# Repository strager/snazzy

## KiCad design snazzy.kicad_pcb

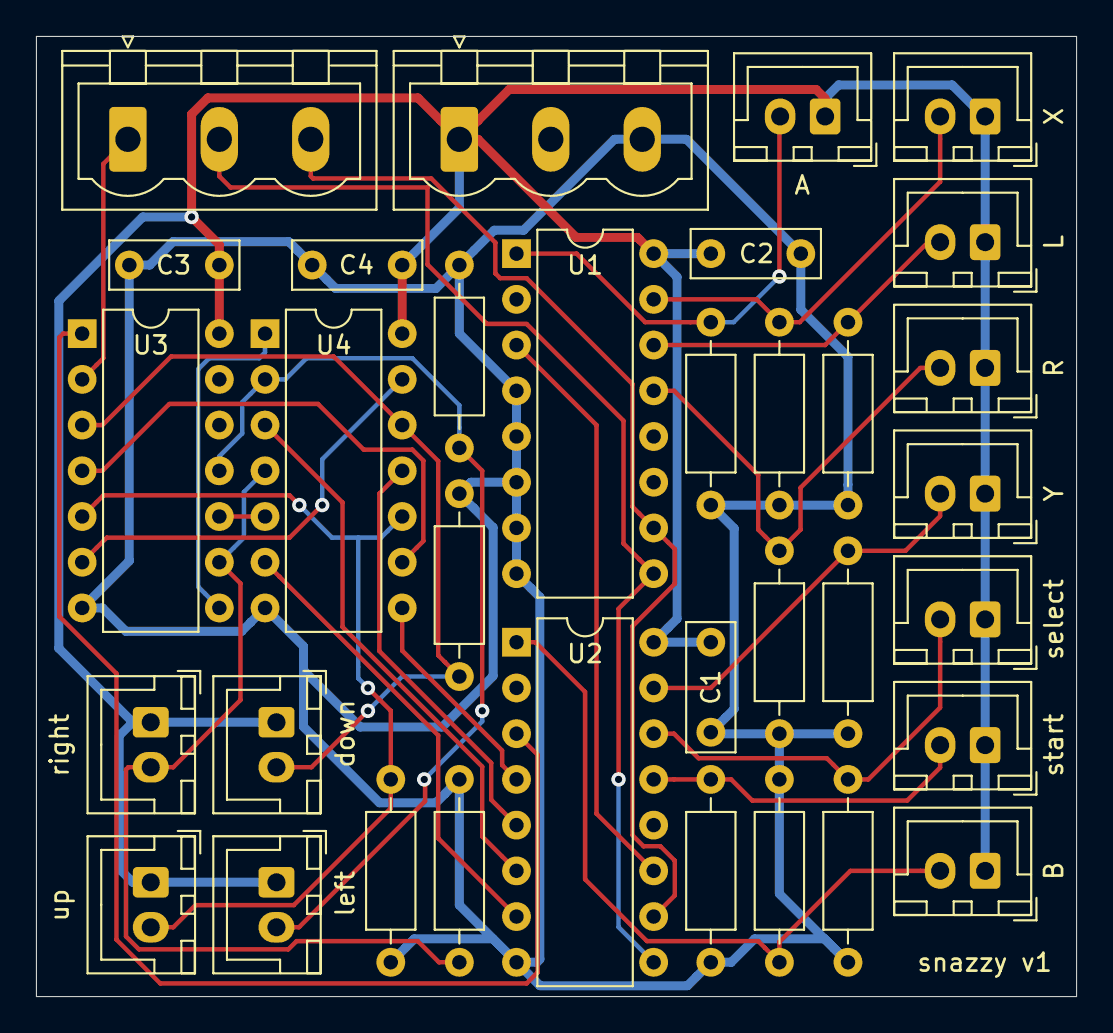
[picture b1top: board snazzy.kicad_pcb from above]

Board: 2 copper layers, 57.8 x 53.3 mm, 34 parts (0 on the bottom side), 27 nets.

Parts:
C1, C2, C3, C4: 100n; C_Rect_L7.0mm_W2.5mm_P5.00mm
J1, J2: Conn_01x03; PhoenixContact_MSTBVA_2,5_3-G-5,08_1x03_P5.08mm_Vertical
R1, R2, R3, R4, R5, R6, R7, R8, R9, R10, R11, R12: 10k; R_Axial_DIN0207_L6.3mm_D2.5mm_P10.16mm_Horizontal
SW1: BTN_START; JST_XH_B2B-XH-A_1x02_P2.50mm_Vertical
SW2: BTN_SELECT; JST_XH_B2B-XH-A_1x02_P2.50mm_Vertical
SW3: BTN_A; JST_XH_B2B-XH-A_1x02_P2.50mm_Vertical
SW4: BTN_B; JST_XH_B2B-XH-A_1x02_P2.50mm_Vertical
SW5: BTN_X; JST_XH_B2B-XH-A_1x02_P2.50mm_Vertical
SW6: BTN_Y; JST_XH_B2B-XH-A_1x02_P2.50mm_Vertical
SW7: BTN_LEFT; JST_XH_B2B-XH-A_1x02_P2.50mm_Vertical
SW8: BTN_RIGHT; JST_XH_B2B-XH-A_1x02_P2.50mm_Vertical
SW9: BTN_UP; JST_XH_B2B-XH-A_1x02_P2.50mm_Vertical
SW10: BTN_DOWN; JST_XH_B2B-XH-A_1x02_P2.50mm_Vertical
SW11: BTN_L; JST_XH_B2B-XH-A_1x02_P2.50mm_Vertical
SW12: BTN_R; JST_XH_B2B-XH-A_1x02_P2.50mm_Vertical
U1, U2: 4021; DIP-16_W7.62mm
U3: 74HC04; DIP-14_W7.62mm
U4: 74HC08; DIP-14_W7.62mm

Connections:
+5V: C1.1, C2.1, C3.1, C4.1, J1.1, SW1.1, SW2.1, SW3.1, SW4.1, SW5.1, SW6.1, SW7.1, SW8.1, SW9.1, SW10.1, SW11.1, SW12.1, U1.16, U2.16, U3.14, U4.14
/BTN_A: R3.1, SW3.2, U1.1
/BTN_B: R4.1, SW4.2, U2.1
/BTN_DOWN: R10.1, SW10.2, U3.3, U4.12
/BTN_L: R11.1, SW11.2, U1.14
/BTN_LEFT: R7.1, SW7.2, U3.11, U4.2
/BTN_R: R12.1, SW12.2, U1.13
/BTN_RIGHT: R8.1, SW8.2, U3.9, U4.4
/BTN_SELECT: R2.1, SW2.2, U2.14
/BTN_START: R1.1, SW1.2, U2.13
/BTN_UP: R9.1, SW9.2, U3.5, U4.10
/BTN_X: R5.1, SW5.2, U1.15
/BTN_Y: R6.1, SW6.2, U2.15
/VBTN_DOWN: U2.5, U4.11
/VBTN_LEFT: U2.6, U4.3
/VBTN_RIGHT: U2.7, U4.6
/VBTN_UP: U2.4, U4.8
GND: C1.2, C2.2, C3.2, C4.2, J1.3, R1.2, R2.2, R3.2, R4.2, R5.2, R6.2, R7.2, R8.2, R9.2, R10.2, R11.2, R12.2, U1.4, U1.5, U1.6, U1.7, U1.8, U2.8, U3.7, U4.7
unnamed: U1.3, U2.11
unnamed: U2.3, U3.1
unnamed: U3.4, U4.9
unnamed: U3.6, U4.13
unnamed: U3.8, U4.1
unnamed: U3.10, U4.5
SNES_clack: J2.3, U1.10, U2.10
SNES_data1: J2.1, U3.2
SNES_latch: J2.2, U1.9, U2.9

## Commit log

2020-03-13 Build a 8-bit shift register
2020-03-13 Simulate SNES latch and clock inputs to controller
2020-03-13 Attach SNES signal generator to controller encoder
2020-03-13 Allow circuit to be driven by CLI
2020-03-13 Separate button inputs into a library; allow substitution for testing
2020-03-16 Test circuit using script
    Use a Python script to run Logisim in validation mode,
    interpret its output, and check that the circuit generates
    the expected data signals.
    The script currently does not configure the circuit's inputs
    (i.e. which buttons are pressed). That will be done in a
    future commit.
2020-03-16 Add more (unwired) buttons to button circuit
2020-03-16 Drive button inputs from test script
    Teach the test script to substitute the buttons circuit
    (buttons.circ) with a circuit generated based on
    configurable button inputs. This will let us programatically
    test as many button inputs as we want.
2020-03-16 Map START, SELECT, B, Y, and d-pad
2020-03-16 Map A, X, L, and R buttons
2020-03-16 Simplify design; remove redundant inverters
2020-03-16 Fix polarity of shift register
2020-03-17 Add schematic of controller
2020-03-17 Annotate components and fix power issues
2020-03-17 Add footprints; split SNES connector into 2 3-pin connectors
2020-03-17 Choose wider resistor footprint for easier assembly
2020-03-17 Place components on PCB
2020-03-17 Add traces to PCB components
2020-03-17 Optimize PCB footprint to save space
2020-03-17 Add capacitor to absorb IC voltage drops
2020-03-17 Logisim: Move inverters next to switches, matching pull-up resistors in real schematic
2020-03-17 Update schematic and PCB (unsure what changed)
2020-03-17 Prevent simultaneous left+right and up+down inputs
2020-03-17 Use pull-down resistors for switches instead
    Using pull-up resistors for the switches requires more
    inverters than I own. Use pull-down resistors instead
    (effectively inverting all switches), reducing the total
    number of inverters required.
2020-03-18 Schematic: Add left^right up^down logic
2020-03-19 PCB: Support left^right and down^up
2020-03-19 Move dimension labels off silkscreen
2020-03-19 Add missing snazzy-vendor library (74HC08)
2020-03-19 PCB: Add revision number silkscreen
2020-03-19 PCB: Clean up traces a bit to reduce ground loops
